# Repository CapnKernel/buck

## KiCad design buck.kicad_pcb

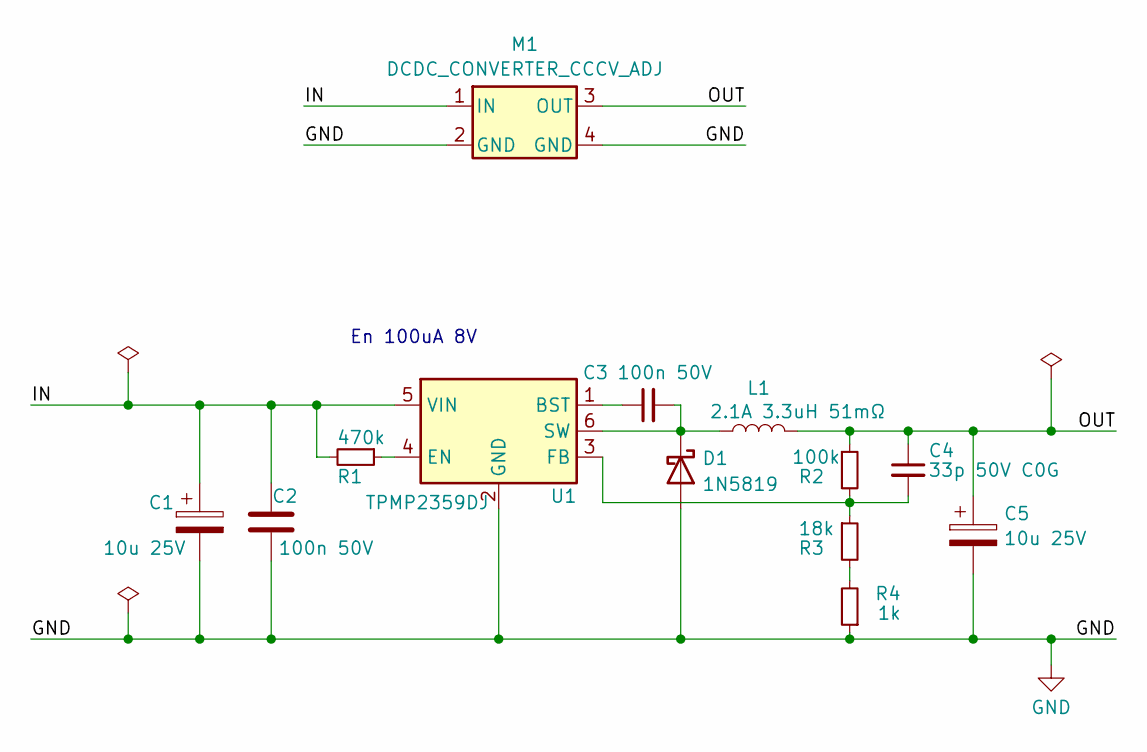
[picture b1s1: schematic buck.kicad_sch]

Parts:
C1, C5: 10u 25V; C_0805_2012Metric
C2, C3: 100n 50V; C_0805_2012Metric; LCSC C14663
C4: 33p 50V C0G; C_0805_2012Metric; LCSC C1663
D1: 1N5819; D_SOD-323; LCSC C191023
L1: 2.1A 3.3uH 51mΩ; L_Shouhan_CY43_5.0x4.5mm; LCSC C2929417
M1: DCDC_CONVERTER_CCCV_ADJ; MP2307_DCDC_CONVERTER
R1: 470k; R_0805_2012Metric; LCSC C23178
R2: 100k; R_0805_2012Metric; LCSC C25803
R3: 18k; R_0805_2012Metric; LCSC C25810
R4: 1k; R_0805_2012Metric; LCSC C21190
U1: TPMP2359DJ; SOT-23-6; LCSC C2959845

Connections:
/IN: C1.1, C2.1, M1.1 (IN), R1.2, U1.5 (VIN)
/OUT: C4.1, C5.1, L1.2, M1.3 (OUT), R2.1
GND: C1.2, C2.2, C5.2, D1.2 (A), M1.2 (GND), M1.4 (GND), R4.1, U1.2 (GND)
unnamed: C3.2, D1.1 (K), L1.1, U1.6 (SW)
unnamed: R3.2, R4.2
unnamed: C3.1, U1.1 (BST)
unnamed: R1.1, U1.4 (EN)
unnamed: C4.2, R2.2, R3.1, U1.3 (FB)

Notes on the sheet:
En 100uA 8V

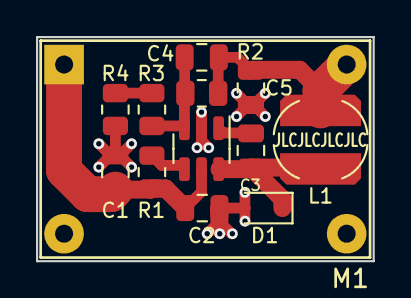
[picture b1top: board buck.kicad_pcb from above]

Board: 2 copper layers, 18.7 x 12.5 mm, 13 parts (0 on the bottom side), 8 nets.

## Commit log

2023-09-16 First revision
2023-09-16 Files to ignore
